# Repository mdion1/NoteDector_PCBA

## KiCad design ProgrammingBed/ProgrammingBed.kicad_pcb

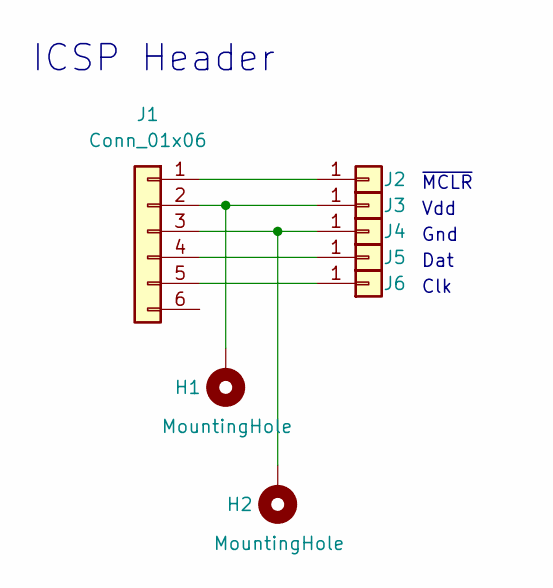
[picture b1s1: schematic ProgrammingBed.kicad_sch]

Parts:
H1, H2: MountingHole; PinHeader_1x01_D1.3mm_Pad2mm
J1: Conn_01x06; PinHeader_1x06_P2.54mm_Vertical
J2, J3, J4, J5, J6: Conn_01x01; PogoPin; Part Number 0985-1-15-20-71-14-11-0

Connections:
unnamed: H1.1, J1.2, J3.1
unnamed: H2.1, J1.3, J4.1
unnamed: J1.1, J2.1
unnamed: J1.4, J5.1
unnamed: J1.5, J6.1

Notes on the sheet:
ICSP Header
~{MCLR}
Dat
Vdd
Clk
Gnd

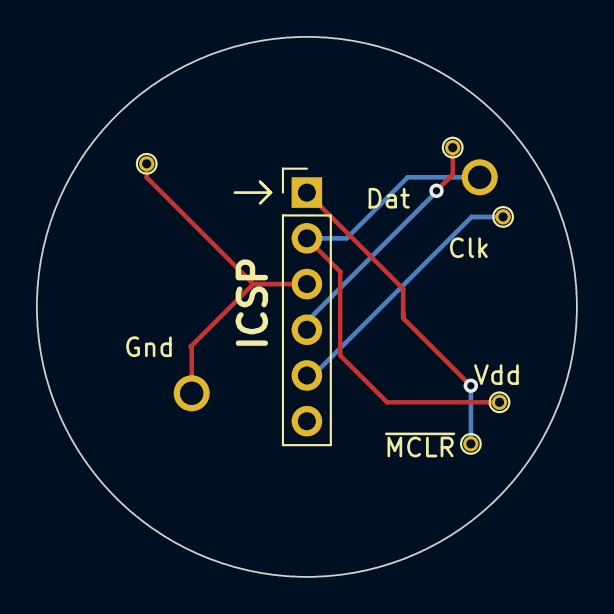
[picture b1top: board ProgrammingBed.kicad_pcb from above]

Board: 2 copper layers, 30.0 x 30.0 mm, 8 parts (0 on the bottom side), 5 nets.

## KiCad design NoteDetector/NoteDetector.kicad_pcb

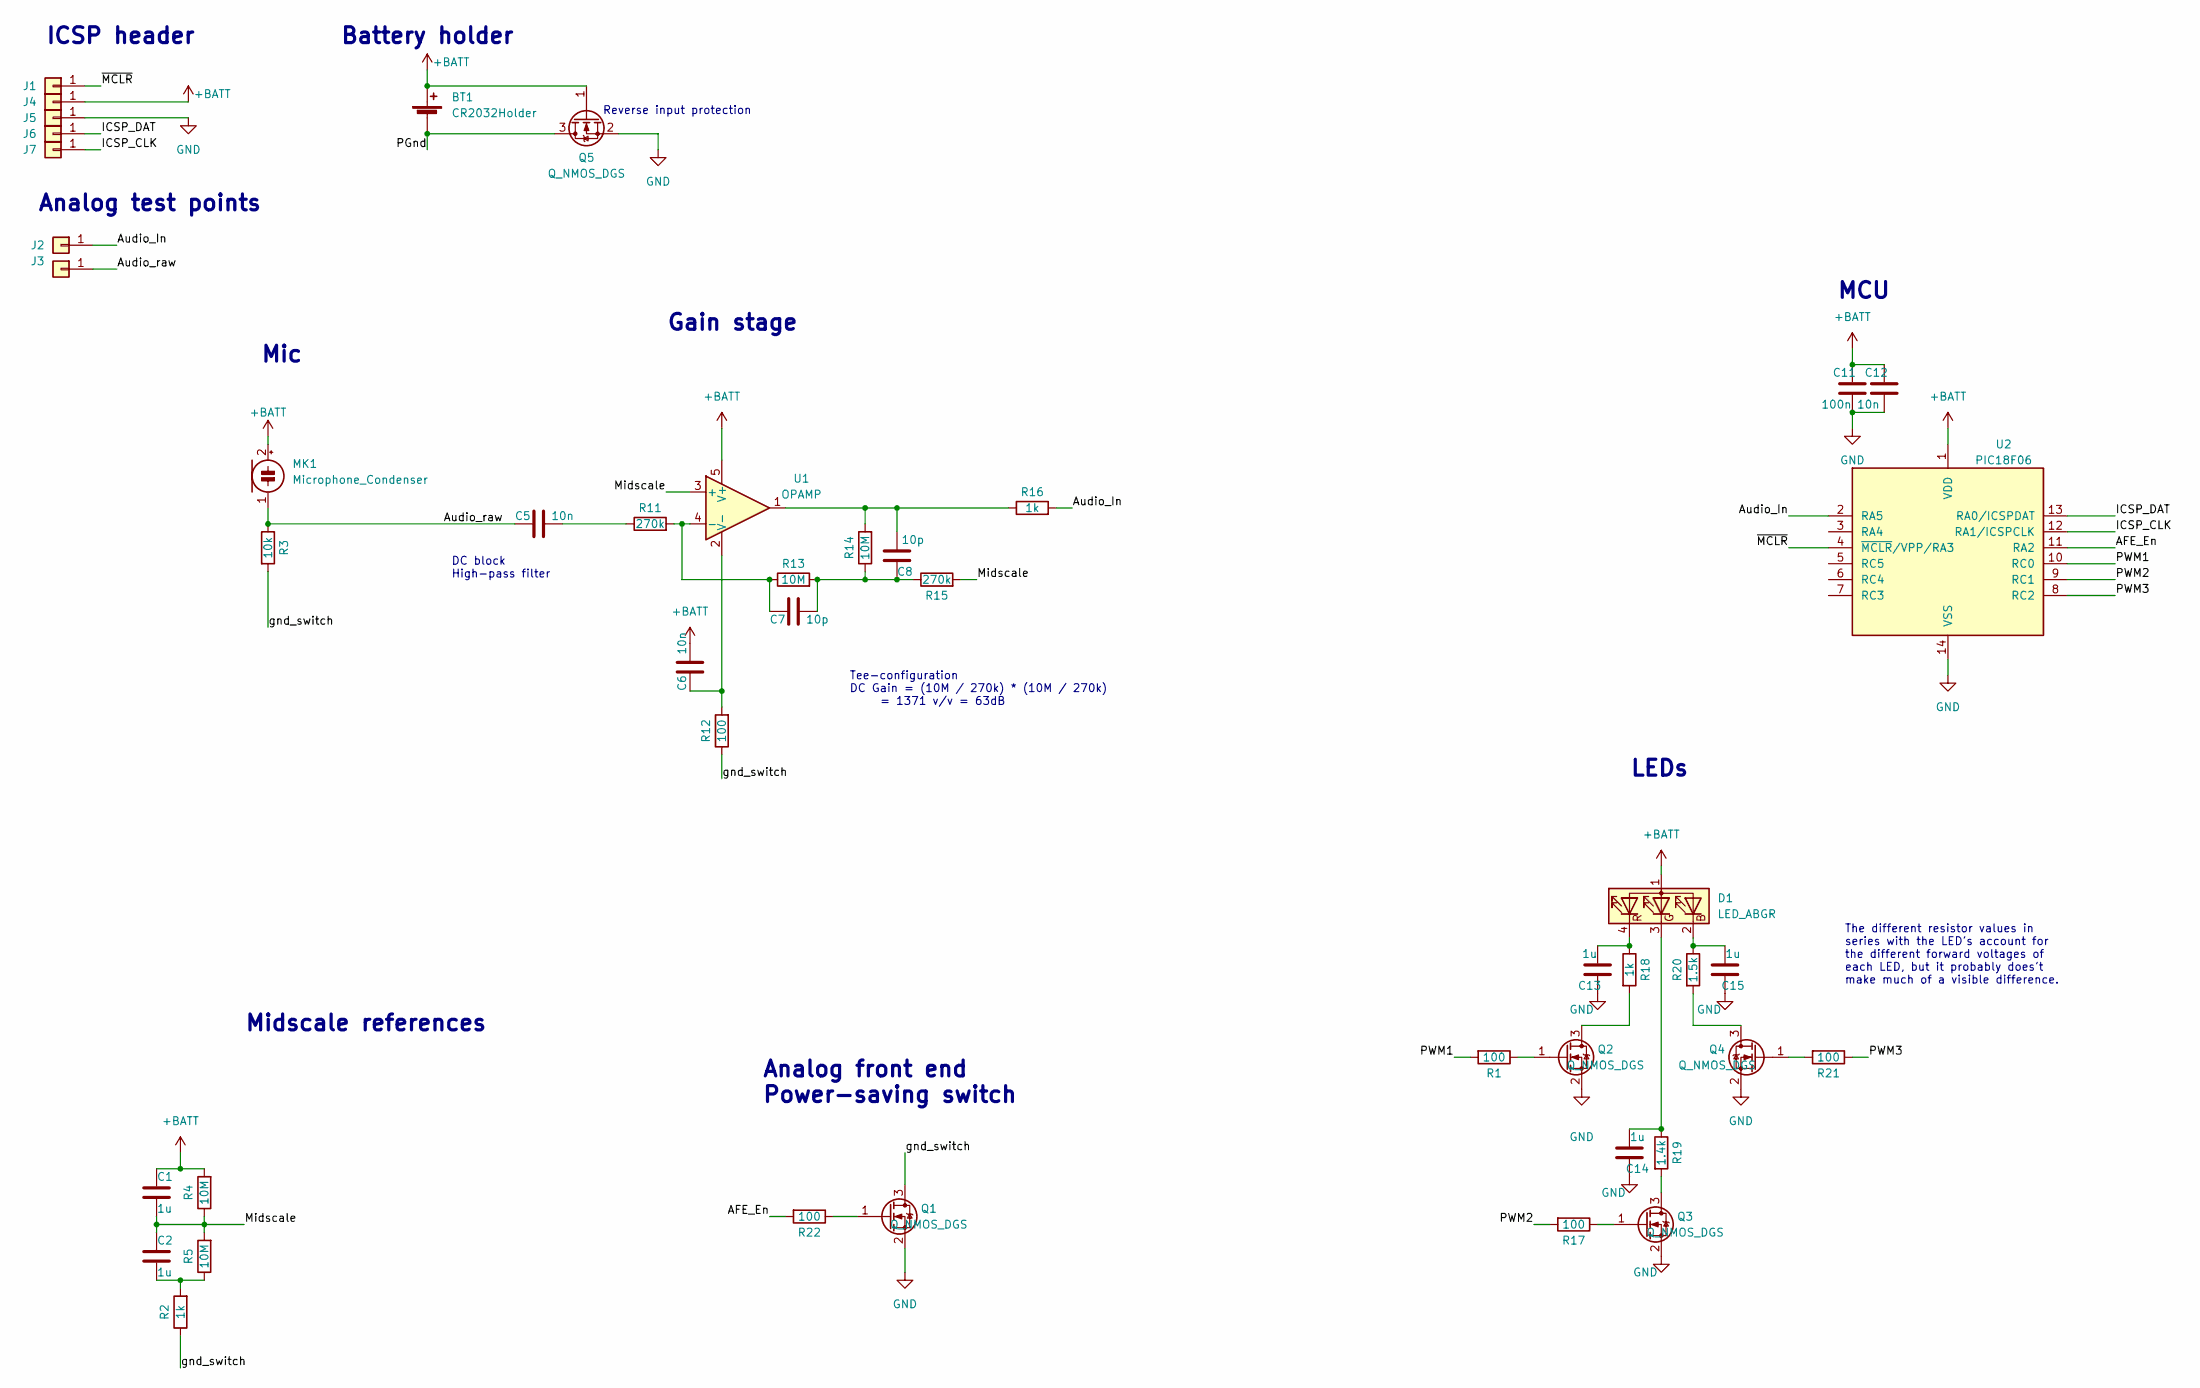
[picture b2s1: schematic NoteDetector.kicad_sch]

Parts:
BT1: CR2032Holder; BH-25C-1; Part Number BH-25C-1
C1, C2, C13, C14, C15: 1u; C_0603_1608Metric; Part Number CL10A105KO8NNND
C5, C6, C12: 10n; C_0603_1608Metric; Part Number 0603B103J500CT
C7, C8: 10p; C_0603_1608Metric; Part Number 0603N100J500CT
C11: 100n; C_0603_1608Metric; Part Number CL10B104JB8NNNC
D1: LED_ABGR; PLCC-4; Part Number CLMVC-FKA-CL1D1L71BB7C3C3
J1, J2, J3, J4, J5, J6, J7: Conn_01x01; TestPoint_Pad_D1.0mm; Part Number none
MK1: Microphone_Condenser; ElectretCondenserMic_SMT_MO063602-1; Part Number MO063602-1
Q1, Q2, Q3, Q4, Q5: Q_NMOS_DGS; SOT-23; Part Number T2N7002AK,LM
R1, R12, R17, R21, R22: 100; R_0603_1608Metric; Part Number CRG0603F100R
R2, R16, R18: 1k; R_0603_1608Metric; Part Number CRCW06031K00FKEAC
R3: 10k; R_0603_1608Metric; Part Number ERJ-3GEYJ103V
R4, R5, R13, R14: 10M; R_0603_1608Metric; Part Number WR06W1005FTL
R11, R15: 270k; R_0603_1608Metric; Part Number RC0603FR-07270KL
R19: 1.4k; R_0603_1608Metric; Part Number CR0603-FX-1401ELF
R20: 1.5k; R_0603_1608Metric; Part Number RC0603JR-131K5L
U1: OPAMP; SOT-23-5; Part Number MCP6061T-E/OT or MCP6231T-E/OT
U2: PIC18F06; TSSOP-14_4.4x5mm_P0.65mm; Part Number PIC18F06Q41-E/ST or PIC18F06Q40-E/ST

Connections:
+BATT: BT1.1 (+), C1.2, C6.1, C11.1, C12.1, D1.1 (A), J4.1, MK1.2 (+), Q5.1 (G), R4.2, U1.5 (V+), U2.1 (VDD)
/AFE_En: R22.2, U2.11 (RA2)
/Audio_In: J2.1, R16.2, U2.2 (RA5)
/Audio_raw: C5.1, J3.1, MK1.1 (-), R3.1
/ICSP_CLK: J7.1, U2.12 (RA1/ICSPCLK)
/ICSP_DAT: J6.1, U2.13 (RA0/ICSPDAT)
/Midscale: C1.1, C2.2, R4.1, R5.2, R15.2, U1.3 (+)
/PGnd: BT1.2 (-), Q5.3 (D)
/PWM1: R1.2, U2.10 (RC0)
/PWM2: R17.2, U2.9 (RC1)
/PWM3: R21.1, U2.8 (RC2)
/gnd_switch: Q1.3 (D), R2.1, R3.2, R12.1
/~MCLR: J1.1, U2.4 (~MCLR/VPP/RA3)
GND: C11.2, C12.2, C13.2, C14.2, C15.2, J5.1, Q1.2 (S), Q2.2 (S), Q3.2 (S), Q4.2 (S), Q5.2 (S), U2.14 (VSS)
unnamed: C2.1, R2.2, R5.1
unnamed: C5.2, R11.1
unnamed: C7.1, C8.2, R13.2, R14.1, R15.1
unnamed: C8.1, R14.2, R16.1, U1.1
unnamed: C15.1, D1.2 (BK), R20.1
unnamed: C14.1, D1.3 (GK), R19.1
unnamed: C13.1, D1.4 (RK), R18.1
unnamed: Q1.1 (G), R22.1
unnamed: Q2.3 (D), R18.2
unnamed: Q2.1 (G), R1.1
unnamed: Q3.3 (D), R19.2
unnamed: Q3.1 (G), R17.1
unnamed: Q4.3 (D), R20.2
unnamed: Q4.1 (G), R21.2
unnamed: C7.2, R11.2, R13.1, U1.4 (-)
unnamed: C6.2, R12.2, U1.2 (V-)

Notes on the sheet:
MCU
Mic
Battery holder
Gain stage
Tee-configuration DC Gain = (10M / 270k) * (10M / 270k) = 1371 v/v = 63dB
The different resistor values in series with the LED's account for the different forward voltages of each LED, but it probably does't make much of a visible difference.
Analog front end Power-saving switch
DC block High-pass filter
Reverse input protection
LEDs
Analog test points
ICSP header
Midscale references

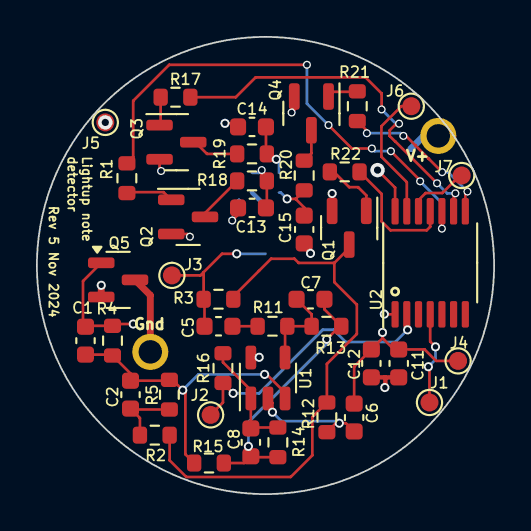
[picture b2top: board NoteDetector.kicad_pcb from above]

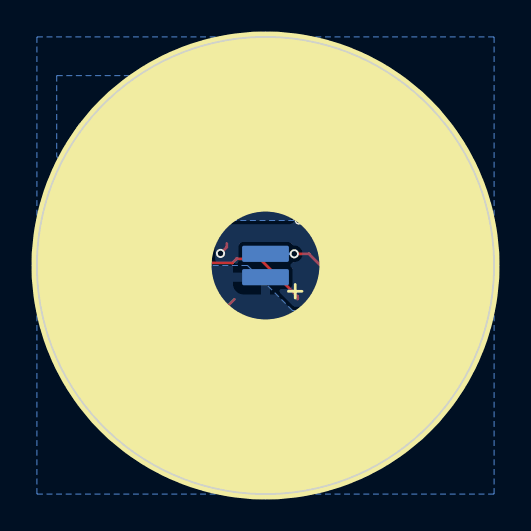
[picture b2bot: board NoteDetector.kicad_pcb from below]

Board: 2 copper layers, 25.4 x 25.4 mm, 45 parts (2 on the bottom side), 30 nets.

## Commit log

2022-02-14 Initial commit: contains finished debugging test board layout
2022-02-14 Started populating BOM
2023-02-03 changed amp circuit
    replacing MEMS mic with electret condenser
    Todo: new microcontroller
2023-02-08 Save work; Added a new schematic symbol for the PIC18F06Q41; new footprint for the MO063602-1 condenser mic
2023-02-09 save work: new layout almost done
2023-02-09 rev2 board layout done
2023-02-09 Added revision to silkscreen
2023-02-20 Added programming bed PCB; moved PCB programming pads; added CR2032 battery holder; todo: fix silkscreen
2023-03-20 Updated BOM, moved programming pads outside of CR2032 battery holder coverage; board layout not finished
2023-03-21 Rev 3 layout (hastily) completed!
2023-03-21 Tweaked layout to get better clearance around programming contact
2023-03-21 Added BOM; added programming bed rev1 layout
2024-11-25 Changelog: combined midscale references; added reverse voltage protection; moved ~MCLR programming pad to board perimeter; increased min drill/pad size
